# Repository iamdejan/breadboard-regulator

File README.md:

# Breadboard Regulator

This project aims to replicate the work of [MB102 breadboard power supply module](https://microcontrollerslab.com/mb102-breadboard-power-supply-module-pinout-and-how-to-use-it/), by receiving input from DC barrel jack and convert it into 5V and 3.3V output.

## Components

- [PRT-10811 DC barrel jack](https://www.tokopedia.com/freelab/socket-dc-in-female-jack-dc-barrel-soket-5-5x2-1mm-pcb)
    - Datasheet:
        - [Sparkfun](https://cdn.sparkfun.com/datasheets/Prototyping/18742.pdf)
        - Input voltage: 9-12V. Usually, 9V is okay, but depending on the diode used, we may need to use 12V.
- [BAT43 Schottky Diode](https://www.tokopedia.com/elantech/bat43-dioda-vishay-small-signal-schottky-diode-bat-43-elantech)
    - Datasheet:
        - [STMicroelectronics](https://www.st.com/resource/en/datasheet/bat42.pdf)
    - In case where Schottky diode is not available, we can use [1N4001 diode](www.tokopedia.com/starlectric/dioda-in4001-1n-4001-in-4001-diode-1n4001).
        - Use 12V input **if** we use 1N4001 diode to compensate for voltage drop.
- [LM7805 IC](https://www.tokopedia.com/starlectric/l7805-lm-7805-lm7805-5v-voltage-tegangan-regulator-l-7805-to-220)
    - Datasheet:
        - [Sparkfun](https://www.sparkfun.com/datasheets/Components/LM7805.pdf)
        - [DatasheetPDF](https://datasheetspdf.com/pdf-file/766812/ThinkiSemiconductor/LM7805/1)
    - Dependencies:
        - Input capacitor (C-in): [0.33 μF polarized capacitor](https://www.tokopedia.com/elantech/elco-0-33uf-50v-nichicon-fg-fine-gold-0-33-uf-kapasitor-elantech)
        - Input-output noise filtering capacitor(s): [0.1 μF ceramic capacitor](https://www.tokopedia.com/cncstorebandung/10pcs-capacitor-ceramic-kapasitor-keramik-100nf-104-0-1uf-50v-10pcs)
        - Output capacitor (C-out): [0.1 μF polarized capacitor](https://www.tokopedia.com/elantech/elco-0-1uf-50v-nichicon-fg-fine-gold-0-1-uf-kapasitor-elantech-fw)
        - Power indicator: [Red LED 5mm](https://www.tokopedia.com/starlectric/led-5mm-merah-5pcs-pack)
        - [Pin header 2.54mm](https://www.tokopedia.com/starlectric/header-pin-1x40-40pin-male)
- [LD1117V33 IC](https://www.tokopedia.com/ecadio/ic-regulator-33v-ld1117v33-ld33v)
    - Datasheet:
        - [Addicore](http://www.st.com/st-web-ui/static/active/en/resource/technical/document/datasheet/CD00000544.pdf)
        - [Sparkfun](https://www.sparkfun.com/datasheets/Components/LD1117V33.pdf)
    - Dependencies:
        - Input-output capacitor (C-in and C-out): [10 μF](https://www.tokopedia.com/elantech/elco-10uf-50v-nichicon-fw-gold-10-uf-kapasitor-capacitor-elantech)
        - Input-output noise filtering capacitor(s): [1 μF](https://www.tokopedia.com/elantech/1uf-105-mlcc-multilayer-ceramic-capacitor-1-uf-kapasitor-elantech)
        - Power indicator: [Red LED 5mm](https://www.tokopedia.com/starlectric/led-5mm-merah-5pcs-pack)
        - [Pin header 2.54mm](https://www.tokopedia.com/starlectric/header-pin-1x40-40pin-male)

## Output

    - +5V and GND male pins.
    - +3.3V and GND male pins.

## How to Use

Open `breadboard-regulator.kicad_pro` file using KiCAD.

NOTE: I'm using KiCAD 7.0.6 for development. Please check if you have the same or compatible version.

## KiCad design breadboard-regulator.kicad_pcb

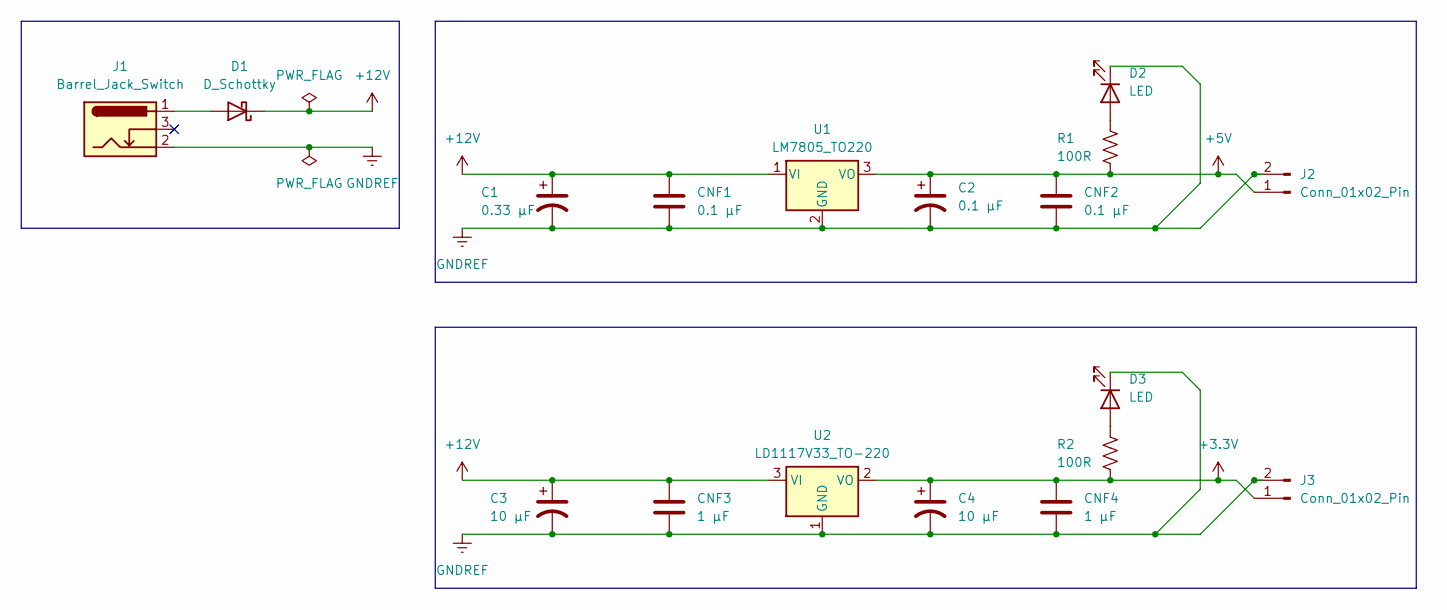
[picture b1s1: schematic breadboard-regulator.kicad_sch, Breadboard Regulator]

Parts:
C1: 0.33 μF; CP_Radial_D5.0mm_P2.50mm
C2: 0.1 μF; CP_Radial_D5.0mm_P2.50mm
C3, C4: 10 μF; CP_Radial_D5.0mm_P2.50mm
CNF1, CNF2: 0.1 μF; C_Disc_D5.0mm_W2.5mm_P5.00mm
CNF3, CNF4: 1 μF; C_Disc_D5.0mm_W2.5mm_P5.00mm
D1: D_Schottky; D_A-405_P7.62mm_Horizontal
D2, D3: LED; LED_D5.0mm
J1: Barrel_Jack_Switch; BarrelJack_Horizontal
J2, J3: Conn_01x02_Pin; PinHeader_1x02_P2.54mm_Vertical
R1, R2: 100R; R_Axial_DIN0207_L6.3mm_D2.5mm_P10.16mm_Horizontal
U1: LM7805_TO220; TO-220-3_Vertical
U2: LD1117V33_TO-220; TO-220-3_Vertical

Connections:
+3.3V: C4.1, CNF4.1, J3.1, R2.2, U2.2 (VO); also elsewhere on the board
+5V: C2.1, CNF2.1, J2.1, R1.2, U1.3 (VO)
+12V: C1.1, C3.1, CNF1.1, CNF3.1, D1.1 (K), U1.1 (VI), U2.3 (VI); also elsewhere on the board
GNDREF: C1.2, C2.2, C3.2, C4.2, CNF1.2, CNF2.2, CNF3.2, CNF4.2, D2.1 (K), D3.1 (K), J1.2, J2.2, J3.2, U1.2 (GND), U2.1 (GND); also elsewhere on the board
unnamed: D1.2 (A), J1.1
unnamed: D2.2 (A), R1.1
unnamed: D3.2 (A), R2.1

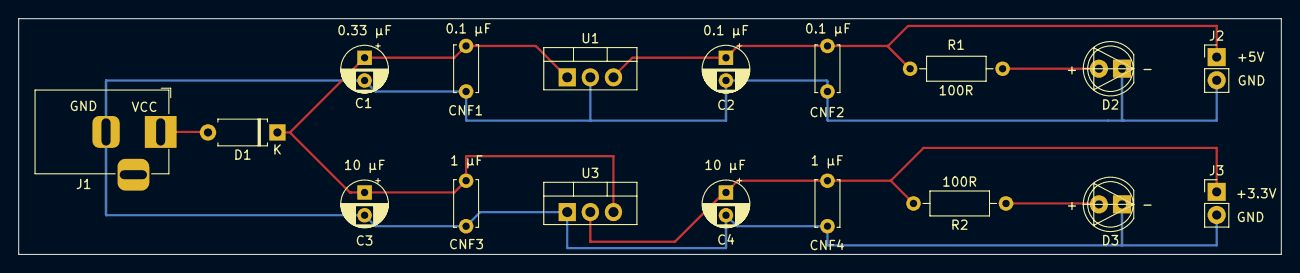
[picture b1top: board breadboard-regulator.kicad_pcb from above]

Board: 2 copper layers, 138.7 x 25.9 mm, 18 parts (0 on the bottom side), 7 nets.

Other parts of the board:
U3: LD1117V33_TO-220; TO-220-3_Vertical

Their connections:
+3.3V: U3.2 (VO); also elsewhere on the board
+12V: U3.3 (VI); also elsewhere on the board
GNDREF: U3.1 (GND); also elsewhere on the board

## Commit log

2023-08-06 add dependencies
2023-08-06 feat: create schematics; create pcb layout
2023-08-06 finish schematic and PCB design
2023-08-06 feat: create schematics; create pcb layout (#1)
2023-08-06 add LED
2023-08-06 Update README.md (#2)
2023-08-06 change wording
2023-08-06 declare output
2023-08-09 split schematics diagram; rearrange PCB
2023-08-09 split schematics diagram; rearrange PCB (#3)
2023-08-13 modify net number
2023-08-13 change from GND to GNDREF
2023-08-13 add diode alternative
2023-08-14 fix component order in README
2023-08-14 fix component order in README (#4)
2023-08-20 Change URL for some components (#5)
2023-08-20 widen solder pad
2023-08-20 add new beginner pin header
2023-08-20 widen solder pad (#6)
2023-08-26 change reference name
